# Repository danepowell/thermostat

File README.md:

<!--
SPDX-FileCopyrightText: 2026 Dane Powell

SPDX-License-Identifier: GPL-3.0-or-later
-->

# ESPHome E-Paper Thermostat

This is an ESPHome touch e-paper thermostat based on the following hardare:

- [XIAO ESP32C6](https://wiki.seeedstudio.com/xiao_esp32c6_getting_started/)
- [Waveshare 2.9in E-Paper Touch HAT](https://www.waveshare.com/2.9inch-Touch-e-Paper-HAT.htm)
- [Pololu U1V11F5 5V regulator](https://www.pololu.com/product/2562)
- 240 mAh 1S LiPo battery

> [!NOTE]
> This is a work in progress and still in a pre-protoype phase. Use at your own risk.

Depends on:

- https://github.com/danepowell/kicad-pololu/

Still in progress:

- Improve battery life (currently only ~5 hours)
- Add a temperature sensor (currently this is more of a remote control than a thermostat, strictly speaking)

The challenge with battery life is the touch sensor and wifi. While the E-Paper display and ESP32 can theoretically go into a deep sleep and consume only a few microamps, this presents two problems:

- We won't receive updates from Home Assistant during this time. One of my biggest grievances with my current IR-based heat pump remote control is that it gets out of sync with changes in Home Assistant, so this is non-negotiable. But maybe we can at least use light sleep and a regular (~15 min) wakeup timer as a compromise.
- The touch display can't be put into any kind of sleep mode without disabling touch updates completely, and it draws quite a bit of power even when idle.

Supposedly the icnt86 touch controller has a low power scan (gesture) wakeup mode that draws only 1-3 mA, which is still more than desired but an order of magnitude less than normal. It could then pulse on INT to wake the ESP32.

Or we could put the icnt86 into deep sleep and poll every ~300 ms. Not actually sure if this would work.

If we ever get to this point, check that our SCL and SDA lines are explicitly put into INPUT_PULLUP on sleep to avoid leakage current.

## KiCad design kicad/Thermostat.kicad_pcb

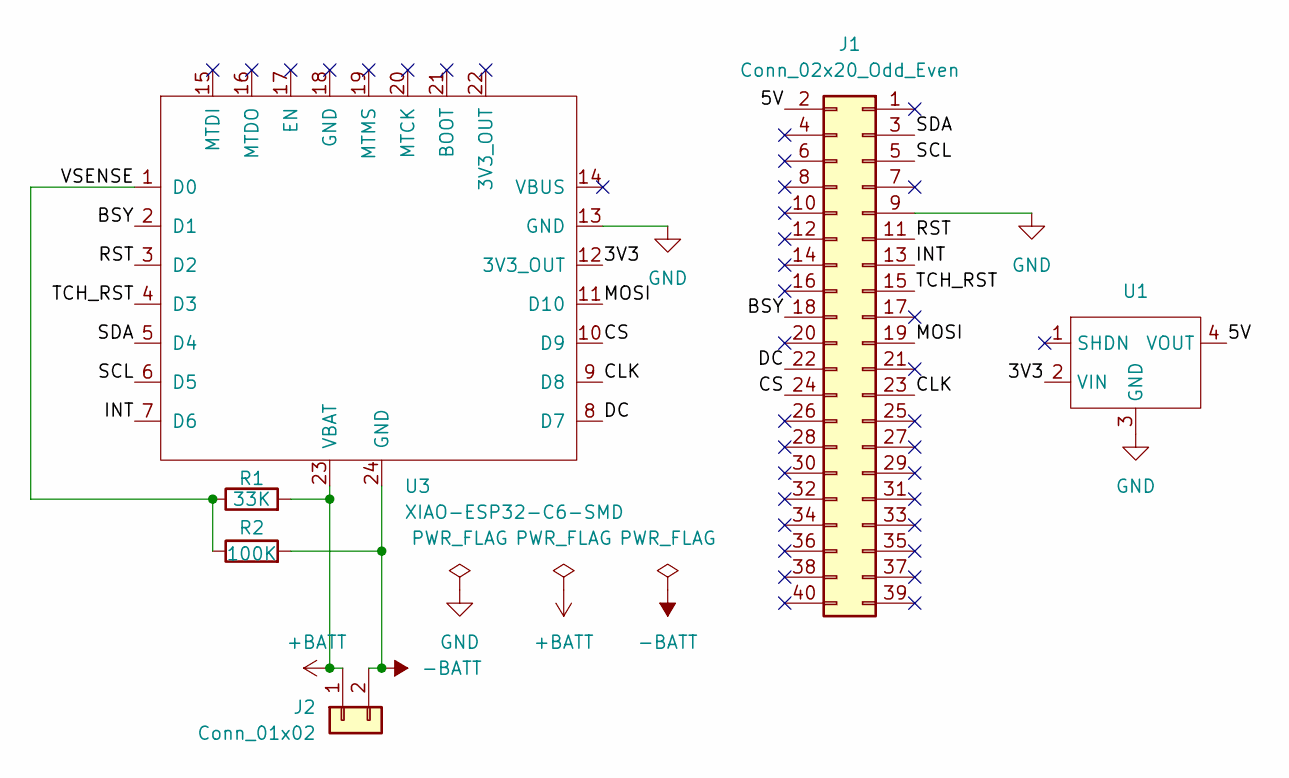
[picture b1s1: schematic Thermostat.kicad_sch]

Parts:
J1: Conn_02x20_Odd_Even; PinHeader_2x20_P2.54mm_Vertical
J2: Conn_01x02; SolderWire-0.25sqmm_1x02_P4.2mm_D0.65mm_OD1.7mm_Relief
R1: 33K; R_Axial_DIN0207_L6.3mm_D2.5mm_P7.62mm_Horizontal
R2: 100K; R_Axial_DIN0207_L6.3mm_D2.5mm_P7.62mm_Horizontal
U1: U1V11F5
U3: XIAO-ESP32-C6-SMD

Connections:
+BATT: J2.1, R1.2, U3.23 (VBAT)
-BATT: J2.2, R2.2, U3.24 (GND)
/3V3: U1.2 (VIN), U3.12 (3V3_OUT)
/5V: J1.2, U1.4 (VOUT)
/BSY: J1.18, U3.2 (D1)
/CLK: J1.23, U3.9 (D8)
/CS: J1.24, U3.10 (D9)
/DC: J1.22, U3.8 (D7)
/INT: J1.13, U3.7 (D6)
/MOSI: J1.19, U3.11 (D10)
/RST: J1.11, U3.3 (D2)
/SCL: J1.5, U3.6 (D5)
/SDA: J1.3, U3.5 (D4)
/TCH_RST: J1.15, U3.4 (D3)
/VSENSE: R1.1, R2.1, U3.1 (D0)
GND: J1.9, U1.3 (GND), U3.13 (GND)

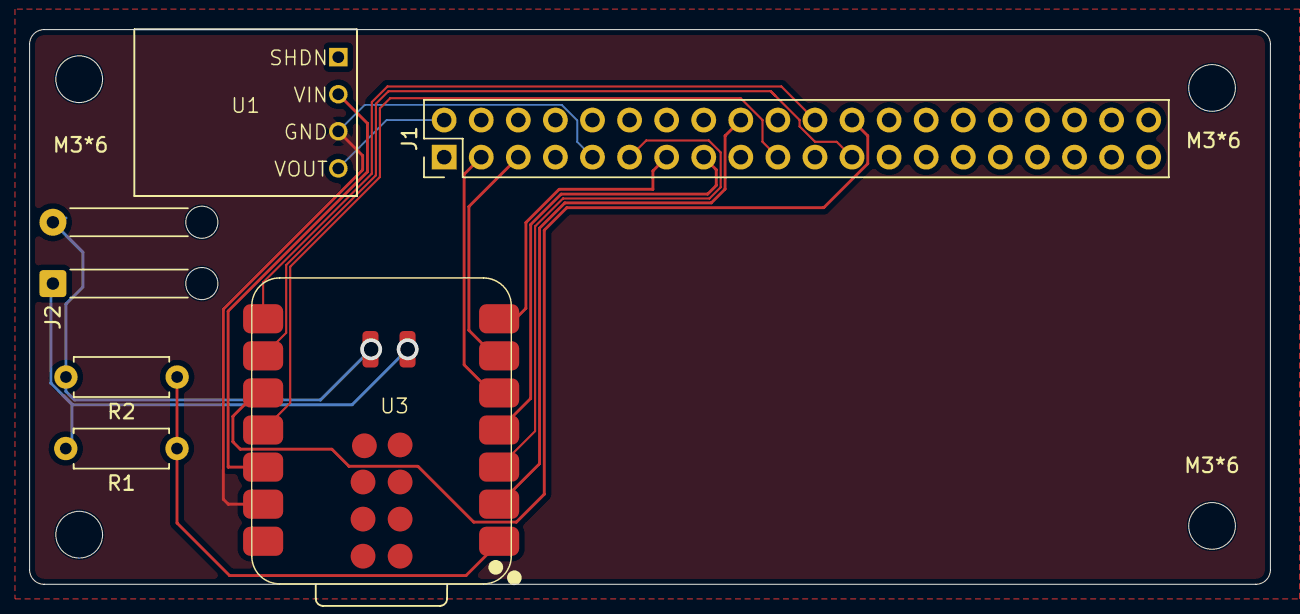
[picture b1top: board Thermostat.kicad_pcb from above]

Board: 4 copper layers, 85.0 x 38.0 mm, 10 parts (0 on the bottom side), 16 nets.

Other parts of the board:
M3*6, M3*6#2, M3*6#3, M3*6#4: MountingHole_3.2mm_M3
